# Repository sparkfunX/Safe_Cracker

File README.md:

SparkFun Safe Cracker
===========================================================

A robot with some tricks to open combination safes.

We were able to crack our Craigslist safe in 40 minutes and 42 seconds! You can [re-watch the live cracking](https://www.youtube.com/watch?v=AsVSEHv2N4M) if you'd like. The magic moment occurs at [45:20](https://www.youtube.com/watch?v=AsVSEHv2N4M&t=45m10s) but start around [44:30](https://www.youtube.com/watch?v=AsVSEHv2N4M&t=44m30s) to get the full scope of what's going on.

The full tutorial is [here](https://learn.sparkfun.com/tutorials/building-a-safe-cracking-robot).

Repository Contents
-------------------

* **/Hardware** - The layout of the Safe Cracker shield in EAGLE PCB
* **/Firmware** - Source code that runs on the [RedBoard](https://www.sparkfun.com/products/13975)
* **/3D** - STL files for the dial coupler, handle puller, nautilus horn, and electronics base plate
* **live_crack_serial.log** - Output from the robot during the live stream.

License Information
-------------------

This project is _**open source**_! 

Please use, reuse, and modify these files as you see fit. Please maintain attribution to SparkFun Electronics and release anything derivative under the same license.

Distributed as-is; no warranty is given.

- Your friends at SparkX

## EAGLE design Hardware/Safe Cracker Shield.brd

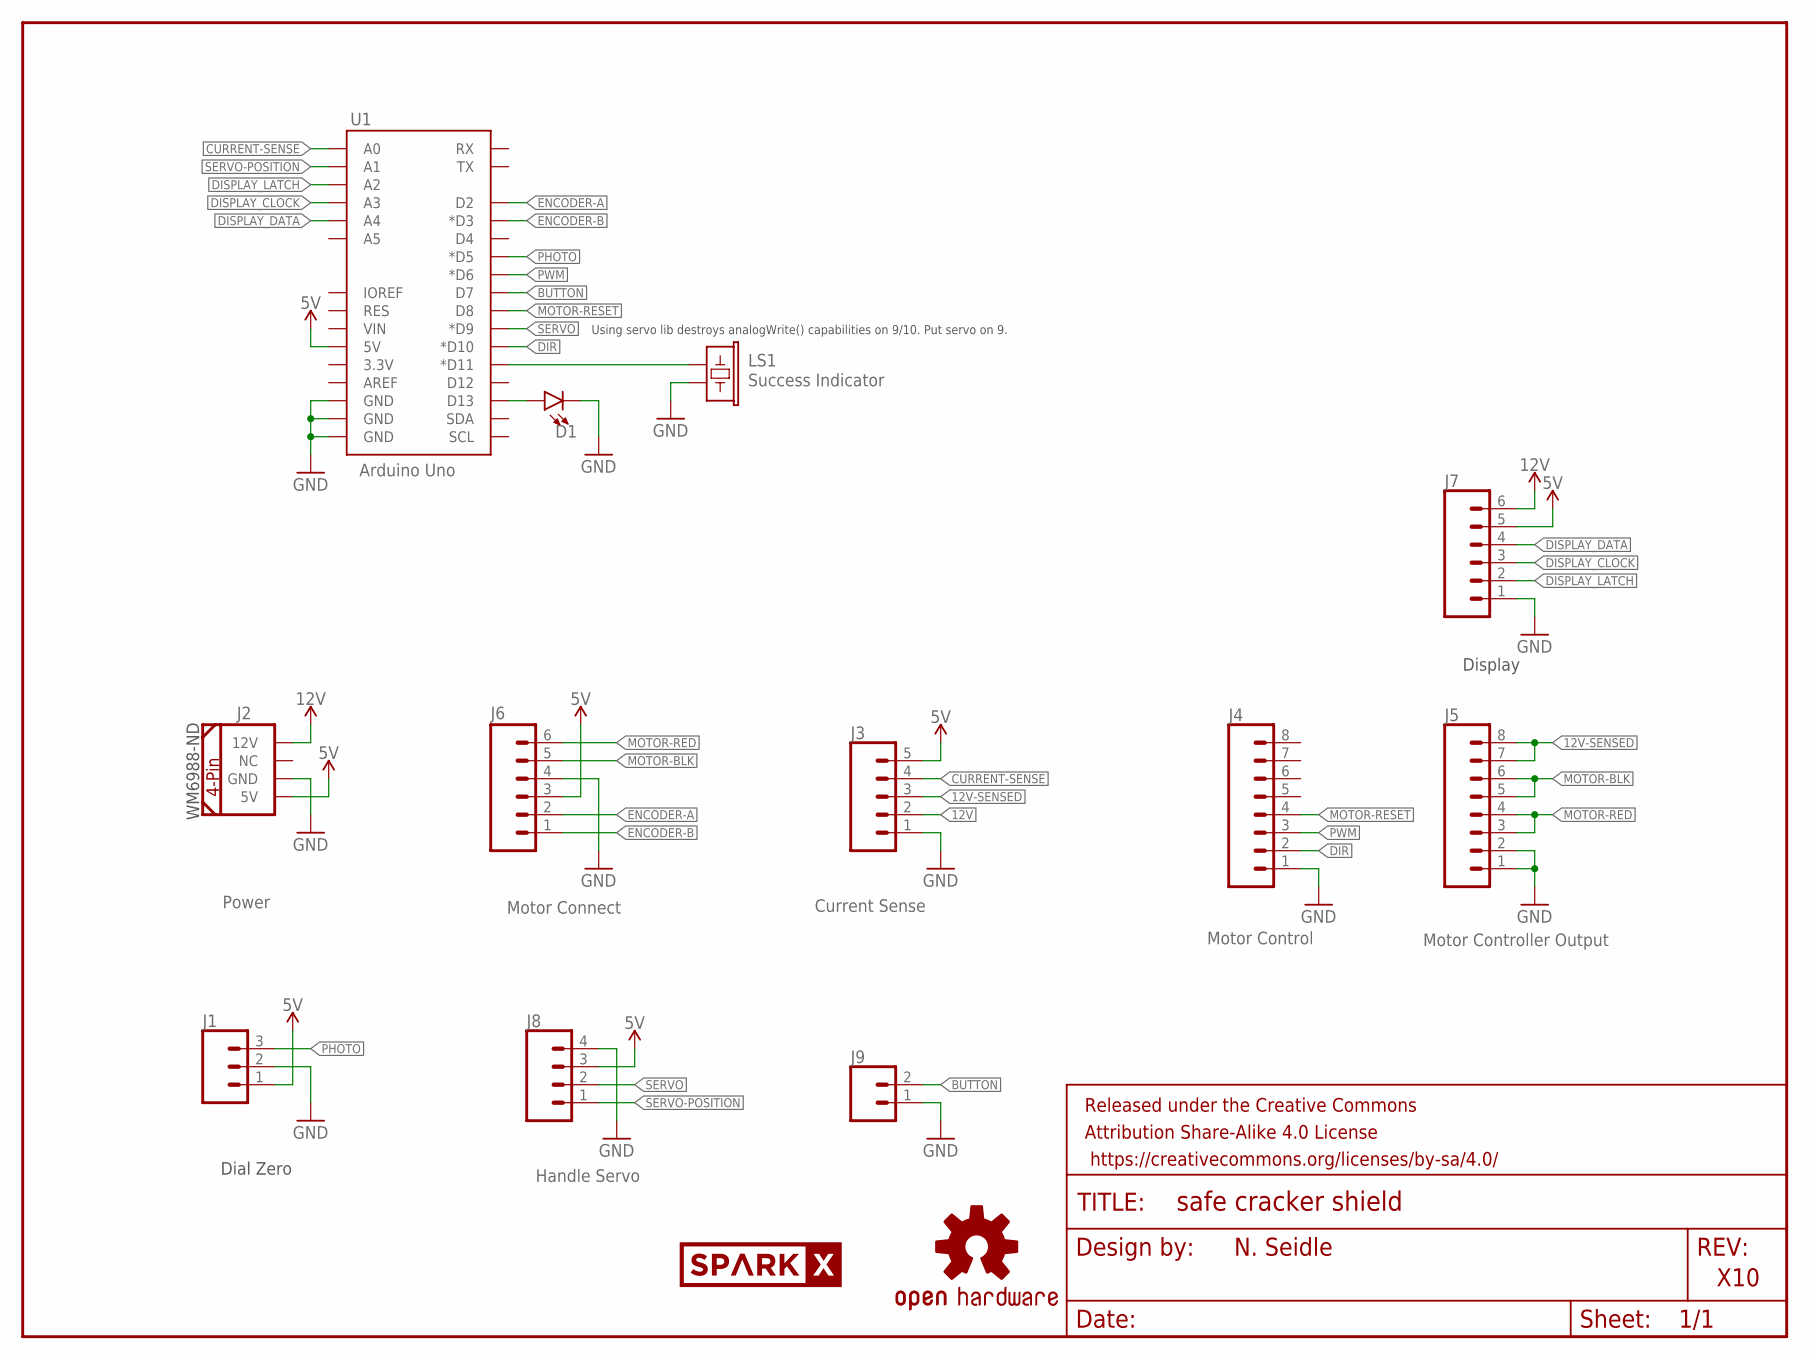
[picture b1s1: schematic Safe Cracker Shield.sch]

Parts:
D1: LED5MM; LED_5MM
FRAME1: FRAME-LETTER; CREATIVE_COMMONS
J1: CONN_03JST-PTH-VERT; JST-3-PTH-VERT
J2: Power; COMPUTER-PERIPHERAL-POWER-RA
J3: Current Sense; 1X05
J4: Motor Control; 1X08
J5: Motor Controller Output; 1X08
J6: Motor Connect; 1X06@1
J7: CONN_06SILK_FEMALE_PTH; 1X06
J8: Handle Servo; 1X04
J9: CONN_02JST-PTH-VERT; JST-2-PTH-VERT
LOGO2: OSHW-LOGOS; OSHW-LOGO-S
LS1: Success Indicator; BUZZER-12MM
U1: Arduino Uno; UNO_R3_SHIELD_NOLABELS
U$1: SPARKX-LOGO5; SPARKX-LARGE

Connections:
5V: J1.1, J2.5V, J3.5, J6.3, J7.5, J8.3, U1.5V
12V: J2.12V, J3.2, J7.6
12V-SENSED: J3.3, J5.7, J5.8
BUTTON: J9.2, U1.D7
BUZZ: LS1.+ (1), U1.D11 (*D11)
CURRENT-SENSE: J3.4, U1.A0
DIR: J4.2, U1.D10 (*D10)
DISPLAY_CLOCK: J7.3, U1.A3
DISPLAY_DATA: J7.4, U1.A4
DISPLAY_LATCH: J7.2, U1.A2
ENCODER-A: J6.2, U1.D2
ENCODER-B: J6.1, U1.D3 (*D3)
GND: D1.K (C), J1.2, J2.GND, J3.1, J4.1, J5.1, J5.2, J6.4, J7.1, J8.4, J9.1, LS1.- (2), U1.GND@0 (GND), U1.GND@1 (GND), U1.GND@2 (GND)
MOTOR-BLK: J5.5, J5.6, J6.5
MOTOR-RED: J5.3, J5.4, J6.6
MOTOR-RESET: J4.4, U1.D8
unnamed: D1.A, U1.D13
PHOTO: J1.3, U1.D5 (*D5)
PWM: J4.3, U1.D6 (*D6)
SERVO: J8.2, U1.D9 (*D9)
SERVO-POSITION: J8.1, U1.A1

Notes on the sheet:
WM6988-ND
N. Seidle
X10
Using servo lib destroys analogWrite() capabilities on 9/10. Put servo on 9.
Dial Zero
Display

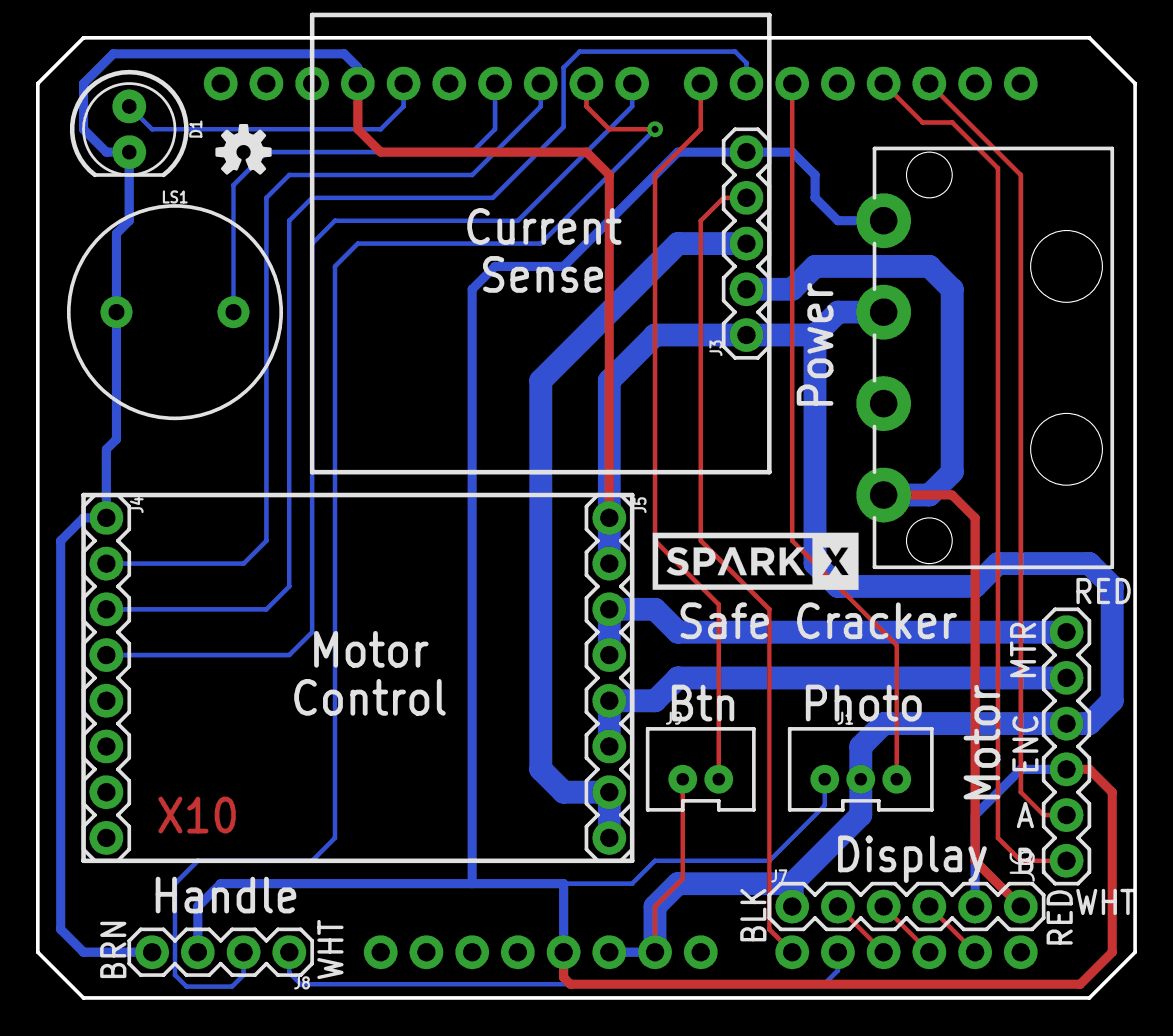
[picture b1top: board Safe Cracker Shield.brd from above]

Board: 2 copper layers, 61.0 x 53.3 mm, 15 parts (0 on the bottom side), 21 nets.

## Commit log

2017-03-04 :neckbeard: Added .gitattributes & .gitignore files
2017-03-04 Initial dial-to-number working code and hardware.
    This code has many debug prints but finds home and dials directly to a
    number (works!).
2017-03-04 Reorg file structure.
2017-03-05 Added display and btn connectors
2017-03-11 Indent measuring is working well. New shield is working well.
2017-03-11 Pretty good and working code.
2017-03-28 Fixed roll over indent count issue. Fixed net names on shield. Working version.
2017-03-28 Fixed net names on display. Clean up hardware directory.
2017-03-28 Adding serial control menu
2017-03-29 Fixing discB/C less than 3 cross over bug.
2017-03-29 Working version. Adding intent selection menu.
2017-03-29 Last commit before live.
2017-03-30 Create STL files
2017-03-30 Adding log from live stream. Adding pdf schematic. Removed old files.
2017-03-30 Adding 3D files
2017-07-11 Adding EEPROM recording of settings
2017-07-12 Indent detection working well. Cracks successfully.
2017-07-23 Find largest indent. New larger servo settings.
    Changed servo to 1/4 scale. Changed handle actuator. Getting offset to
    work correctly. General clean up.
2017-07-24 Convert to button for handle detection.
    Successfully cracks.
2017-07-24 Interference widths now working.
    DiscB now stops testing before interefering with discA. DiscC testing
    now works thru full set test without affecting discB.
2017-07-24 Adding button testing function
    Used to calibrate height of success button
2017-07-24 Adding servo settings storage in EEPROM
2017-07-25 discB now behaves correctly during crossover of C.
    Reducing speed to increase accuracy. System now goes past 99 if
    necessary.
2017-07-25 Add files via upload
    Adding new Dial Knob .stl file for the SentrySafe model #SFW123DTB
2017-07-26 Fixed indentToTry recording bug

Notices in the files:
parts and their libraries:
SparkFun-Aesthetics: Licensing: CC v3.0 Share-Alike You are welcome to use this library for commercial purposes.
SparkFun-Aesthetics: Released under the Creative Commons Attribution Share-Alike 4.0 License
SparkFun-Aesthetics: https://creativecommons.org/licenses/by-sa/4.0
